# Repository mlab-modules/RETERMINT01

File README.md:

# RETERMINT01 – RETERMINAL DM Interface Board

<div align="center">

</div>

RETERMINT01 is an interface board for the [reTerminal DM](https://wiki.seeedstudio.com/reterminal-dm/) by Seeed Studio. It adds a galvanically isolated industrial interface — **3× RS-485** bus, **isolated 24 V power supply** and the ability to **remotely switch off the power** of a connected field device via GPIO. All communication on the bus side is fully galvanically isolated from the reTerminal DM logic.

The board connects directly to the 40-pin GPIO header of the reTerminal DM.

## Features

- **3× RS-485** – galvanically isolated half-duplex channels (ADM2483xRW), up to 500 kbps
- **Isolated 24 V DC/DC** – 30 W Traco Power THN 30-2423WI, software-controllable (default OFF)
- **Remote power switching** – PS1 output controlled via `PWR_OFF` GPIO signal (active LOW)
- **5 V power module** – TI TPSM33606S5, powers the isolated RS-485 bus side
- **u-blox NEO-M9N GPS** – with u.FL antenna connector, USB configuration port and 1 F supercapacitor backup
- **Shielded RJ45 with LEDs** – for RS-485 field bus connection
- **ESD & overvoltage protection** – SM712 TVS on every RS-485 channel, USBLC6-2SC6 on GPS USB
- **2× 1 A fuse** – on 24 V input paths

## Schematic

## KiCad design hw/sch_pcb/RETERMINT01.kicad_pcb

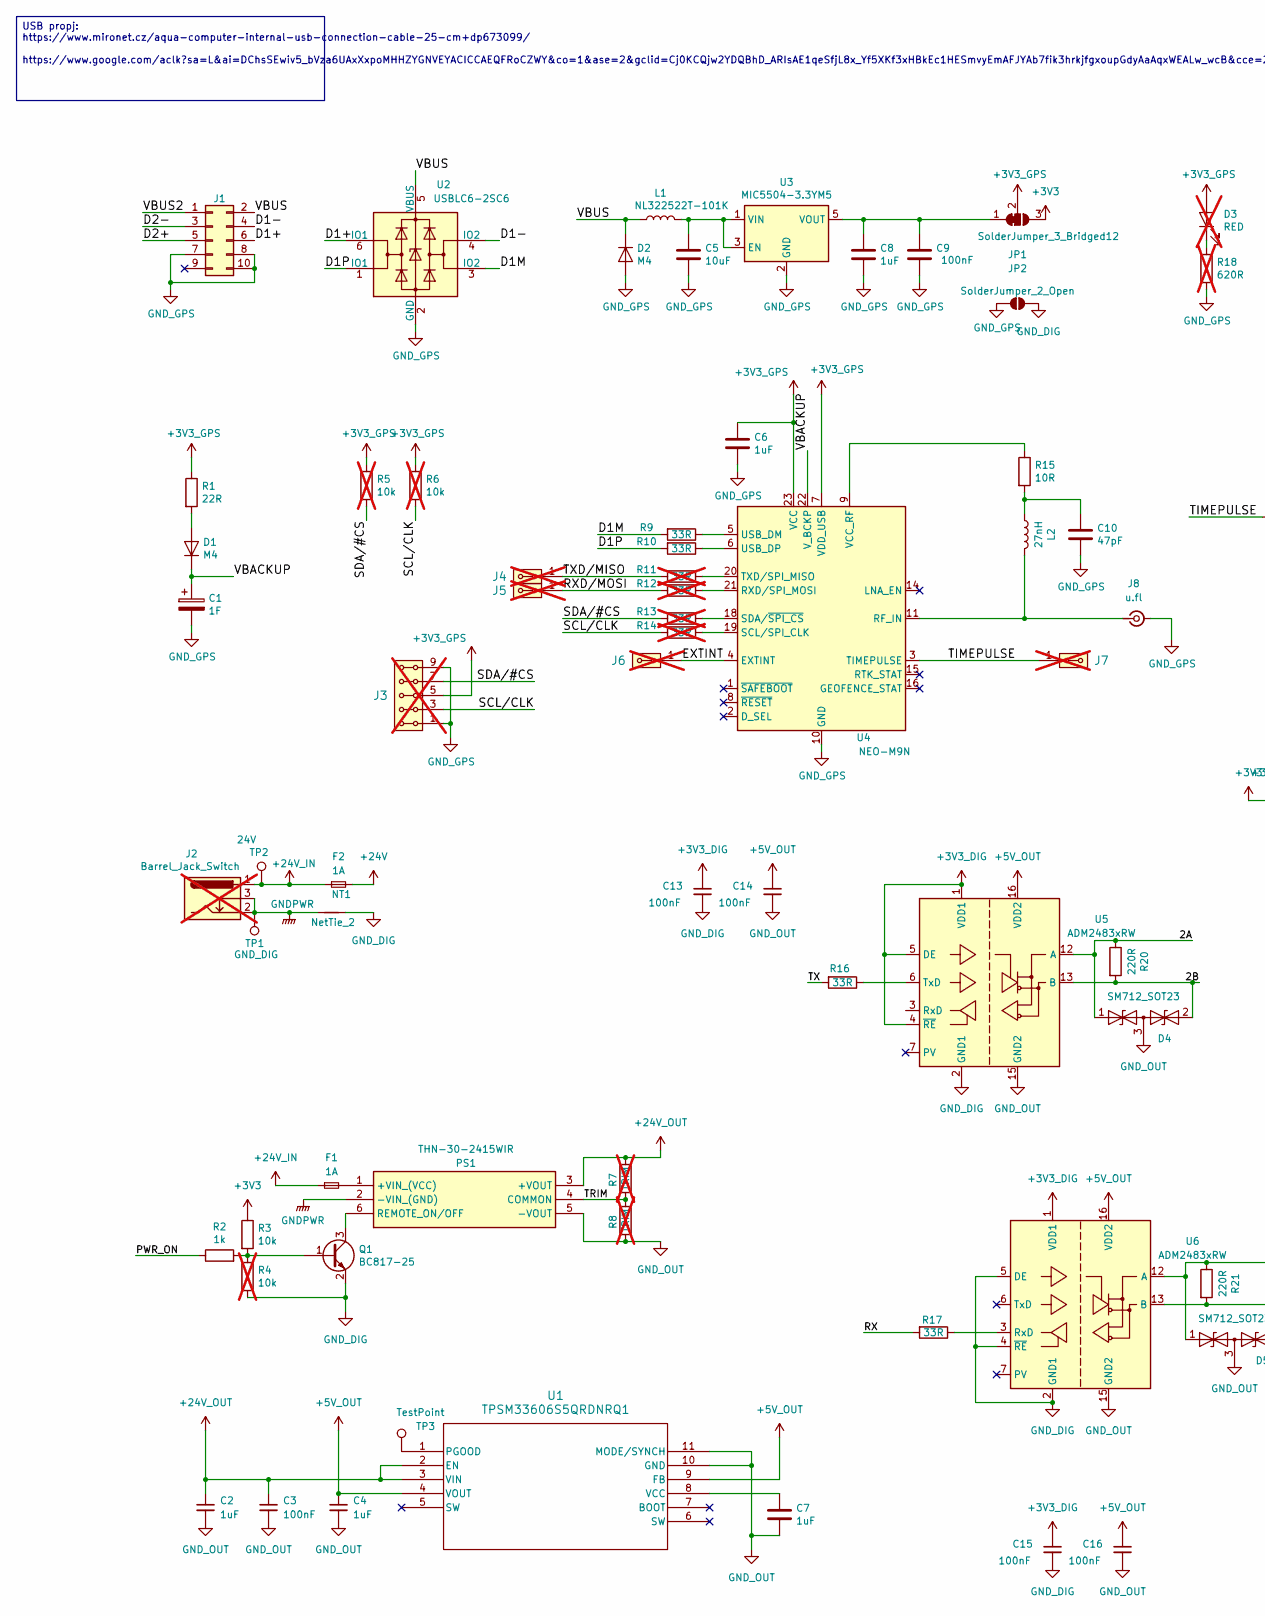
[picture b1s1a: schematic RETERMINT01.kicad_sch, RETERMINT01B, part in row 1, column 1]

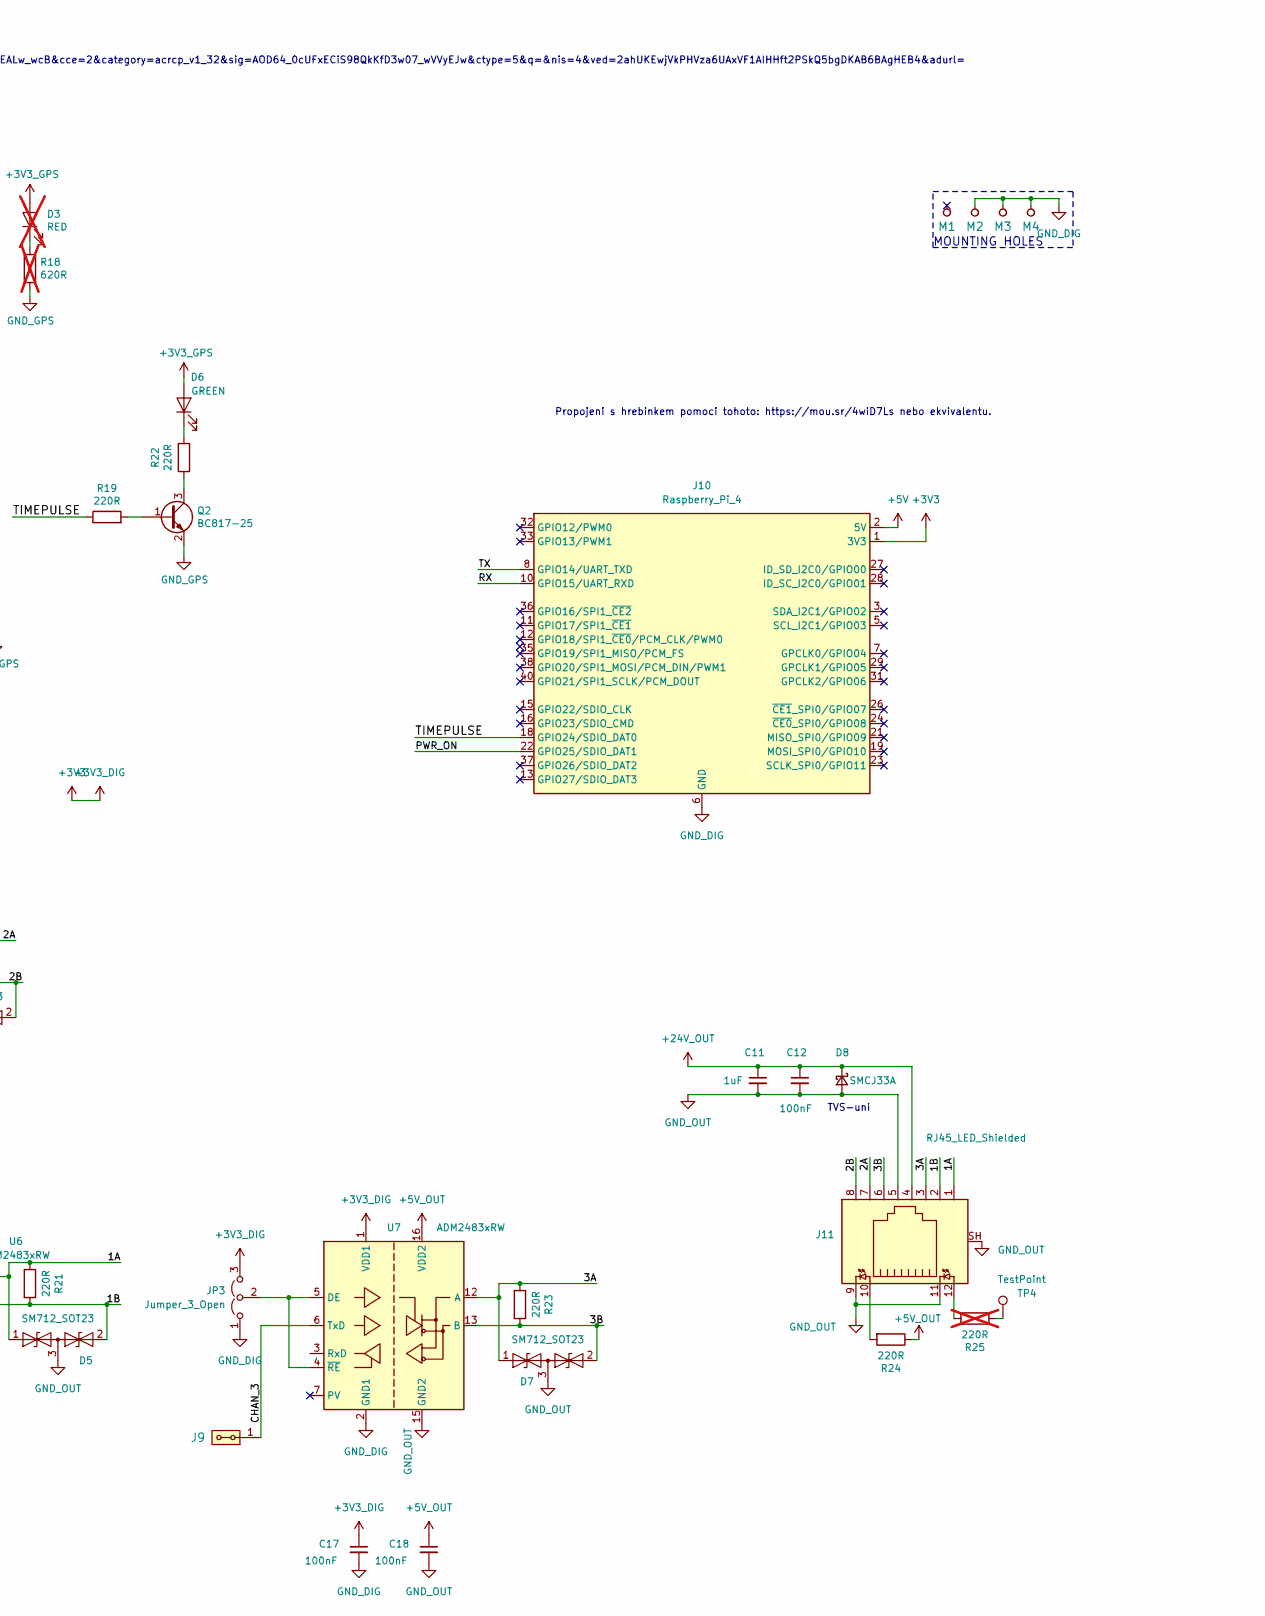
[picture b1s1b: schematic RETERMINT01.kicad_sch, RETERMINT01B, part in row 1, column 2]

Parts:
C1: 1F; CP_Radial_D8.0mm_P3.50mm
C2, C4, C6, C7, C8, C11: 1uF; C_0805_2012Metric
C3, C9, C12, C13, C14, C15, C16, C17, C18: 100nF; C_0805_2012Metric
C5: 10uF; C_0805_2012Metric
C10: 47pF; C_0805_2012Metric
D1, D2: M4; D_SMA
D3: RED; LED_1206_3216Metric; not fitted
D4, D5, D7: SM712_SOT23; SOT-23
D6: GREEN; LED_1206_3216Metric
D8: SMCJ33A; D_SMC
F1, F2: 1A; Fuse_0805_2012Metric
J1: Conn_02x05_Odd_Even; PinHeader_2x05_P2.54mm_Vertical
J2: Barrel_Jack_Switch; BarrelJack_Horizontal; not fitted
J3: HEADER_2x05_PARALLEL; Straight_2x05; not fitted
J4, J5, J6, J7: HEADER_2x01_PARALLEL; Straight_2x01; not fitted
J8: u.fl; U.FL_Molex_MCRF_73412-0110_Vertical
J9: HEADER_2x01_PARALLEL; Straight_2x01
J10: Raspberry_Pi_4; PinHeader_2x20_P2.54mm_Vertical
J11: RJ45_LED_Shielded; RJ45_Amphenol_RJHSE538X
JP1: SolderJumper_3_Bridged12; SolderJumper-3_P1.3mm_Bridged12_RoundedPad1.0x1.5mm
JP2: SolderJumper_2_Open; SolderJumper-2_P1.3mm_Open_RoundedPad1.0x1.5mm
JP3: Jumper_3_Open; PinHeader_1x03_P2.54mm_Vertical
L1: NL322522T-101K; L_1210_3225Metric
L2: 27nH; L_0402_1005Metric
M1, M2, M3, M4: HOLE; MountingHole_3mm
NT1: NetTie_2; NetTie-2_SMD_Pad0.5mm
PS1: THN-30-2415WIR; Converter_DCDC_TRACO_THN30-xxxx_THT; Mouser Part Number 495-THN30-2415WIR
Q1, Q2: BC817-25; SOT-23
R1: 22R; R_0805_2012Metric
R2: 1k; R_0805_2012Metric
R3: 10k; R_0805_2012Metric
R4, R5, R6: 10k; R_0805_2012Metric; not fitted
R7, R8: TRIM; R_0805_2012Metric; not fitted
R9, R10, R16, R17: 33R; R_0805_2012Metric
R11, R12, R13, R14: 33R; R_0805_2012Metric; not fitted
R15: 10R; R_0805_2012Metric
R18: 620R; R_0805_2012Metric; not fitted
R19, R20, R21, R22, R23, R24: 220R; R_0805_2012Metric
R25: 220R; R_0805_2012Metric; not fitted
TP1: GND_DIG; Pin_D1.4mm_L8.5mm_W2.8mm_FlatFork
TP2: 24V; Pin_D1.4mm_L8.5mm_W2.8mm_FlatFork
TP3, TP4: TestPoint; TestPoint_Pad_D1.5mm
U1: TPSM33606S5QRDNRQ1; RDN0011A_TEX
U2: USBLC6-2SC6; SOT-23-6
U3: MIC5504-3.3YM5; SOT-23-5
U4: NEO-M9N; ublox_NEO
U5, U6, U7: ADM2483xRW; SOIC-16W_7.5x10.3mm_P1.27mm

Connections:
+3V3: C13.1, C15.1, C17.1, J10.1 (3V3), J10.17 (3V3), JP1.3 (B), JP3.3 (B), R3.1, U5.1 (VDD1), U5.4 (~RE), U5.5 (DE), U6.1 (VDD1), U7.1 (VDD1)
+3V3_GPS: C6.1, D3.2 (A), D6.2 (A), J3.5, J3.6, JP1.2 (C), R1.1, R5.1, R6.1, U4.7 (VDD_USB), U4.23 (VCC)
+5V: J10.2 (5V), J10.4 (5V)
+5V_OUT: C4.1, C14.1, C16.1, C18.1, R24.1, U1.4 (VOUT), U1.9 (FB), U5.16 (VDD2), U6.16 (VDD2), U7.16 (VDD2)
+24V: F2.2
+24V_IN: F1.1, F2.1, J2.1, TP2.1 (1_1)
+24V_OUT: C2.1, C3.1, C11.1, C12.1, D8.1 (K), J11.4, PS1.3 (+VOUT), R7.1, U1.2 (EN), U1.3 (VIN)
/1A: D5.1 (A1), J11.1, R21.1, U6.12 (A)
/1B: D5.2 (A2), J11.2, R21.2, U6.13 (B)
/2A: D4.1 (A1), J11.7, R20.1, U5.12 (A)
/2B: D4.2 (A2), J11.8, R20.2, U5.13 (B)
/3A: D7.1 (A1), J11.3, R23.1, U7.12 (A)
/3B: D7.2 (A2), J11.6, R23.2, U7.13 (B)
/CHAN_3: J9.1, J9.2, U7.6 (TxD)
/D1+: J1.6, U2.6 (IO1)
/D1-: J1.4, U2.4 (IO2)
/D1M: R9.2, U2.3 (IO2)
/D1P: R10.2, U2.1 (IO1)
/D2+: J1.5
/D2-: J1.3
/EXTINT: J6.1, J6.2, U4.4 (EXTINT)
/PWR_ON: J10.22 (GPIO25/SDIO_DAT1), R2.1
/RX: J10.10 (GPIO15/UART_RXD), R17.2
/RXD/MOSI: J5.1, J5.2, R12.2
/SCL/CLK: J3.3, J3.4, R6.2, R14.2
/SDA/#CS: J3.7, J3.8, R5.2, R13.2
/TIMEPULSE: J7.1, J7.2, J10.18 (GPIO24/SDIO_DAT0), R19.1, U4.3 (TIMEPULSE)
/TRIM: PS1.4 (COMMON), R7.2, R8.1
/TX: J10.8 (GPIO14/UART_TXD), R16.2
/TXD/MISO: J4.1, J4.2, R11.2
/VBACKUP: C1.1, D1.1 (K), U4.22 (V_BCKP)
/VBUS: D2.1 (K), J1.2, L1.1, U2.5 (VBUS)
/VBUS2: J1.1
GNDPWR: J2.2, J2.3, NT1.1, PS1.2 (-VIN_(GND)), TP1.1 (1_1)
GND_DIG: C13.2, C15.2, C17.2, J10.6 (GND), J10.9 (GND), J10.14 (GND), J10.20 (GND), J10.25 (GND), J10.30 (GND), J10.34 (GND), J10.39 (GND), JP2.2 (B), JP3.1 (A), M2.1, M3.1, M4.1, NT1.2, Q1.2 (E), R4.2, U5.2 (GND1), U5.8 (GND1), U6.2 (GND1), U6.4 (~RE), U6.5 (DE), U6.8 (GND1), U7.2 (GND1), U7.8 (GND1)
GND_GPS: C1.2, C5.2, C6.2, C8.2, C9.2, C10.2, D2.2 (A), J1.7, J1.8, J1.10, J3.1, J3.2, J3.9, J3.10, J8.2 (Ext), JP2.1 (A), Q2.2 (E), R18.2, U2.2 (GND), U3.2 (GND), U4.10 (GND), U4.12 (GND), U4.13 (GND), U4.24 (GND)
GND_OUT: C2.2, C3.2, C4.2, C7.2, C11.2, C12.2, C14.2, C16.2, C18.2, D4.3 (common), D5.3 (common), D7.3 (common), D8.2 (A), J11.5, J11.9, J11.11, J11.SH, PS1.5 (-VOUT), R8.2, U1.10 (GND), U1.11 (MODE/SYNCH), U5.9 (GND2), U5.15 (GND2), U6.9 (GND2), U6.15 (GND2), U7.9 (GND2), U7.15 (GND2)
unnamed: C10.1, L2.1, R15.2
unnamed: D1.2 (A), R1.2
unnamed: D3.1 (K), R18.1
unnamed: D6.1 (K), R22.2
unnamed: J8.1 (In), L2.2, U4.11 (RF_IN)
unnamed: J11.10, R24.2
unnamed: J11.12, R25.2
unnamed: C8.1, C9.1, JP1.1 (A), U3.5 (VOUT)
unnamed: JP3.2 (C), U7.4 (~RE), U7.5 (DE)
unnamed: F1.2, PS1.1 (+VIN_(VCC))
unnamed: PS1.6 (REMOTE_ON/OFF), Q1.3 (C)
unnamed: Q1.1 (B), R2.2, R3.2, R4.1
unnamed: Q2.1 (B), R19.2
unnamed: Q2.3 (C), R22.1
unnamed: R25.1, TP4.1 (1_1)
unnamed: TP3.1 (1_1), U1.1 (PGOOD)
unnamed: C7.1, U1.8 (VCC)
unnamed: C5.1, L1.2, U3.1 (VIN), U3.3 (EN)
unnamed: R12.1, U4.21 (RXD/SPI_MOSI)
unnamed: R14.1, U4.19 (SCL/SPI_CLK)
unnamed: R13.1, U4.18 (SDA/~SPI_CS)
unnamed: R11.1, U4.20 (TXD/SPI_MISO)
unnamed: R9.1, U4.5 (USB_DM)
unnamed: R10.1, U4.6 (USB_DP)
unnamed: R15.1, U4.9 (VCC_RF)
unnamed: R16.1, U5.6 (TxD)
unnamed: R17.1, U6.3 (RxD)

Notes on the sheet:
Propojeni s hrebinkem pomoci tohoto: https://mou.sr/4wiD7Ls nebo ekvivalentu.
TVS-uni
MOUNTING HOLES
USB propj: https://www.mironet.cz/aqua-computer-internal-usb-connection-cable-25-cm+dp673099/ https://www.google.com/aclk?sa=L&ai=DChsSEwiv5_bVza6UAxXxpoMHHZYGNVEYACICCAEQFRoCZWY&co=1&ase=2&gclid=Cj0KCQjw2YDQBhD_ARIsAE1qeSfjL8x_Yf5XKf3xHBkEc1HESmvyEmAFJYAb7fik3hrkjfgxoupGdyAaAqxWEALw_wcB&cce=2&cate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

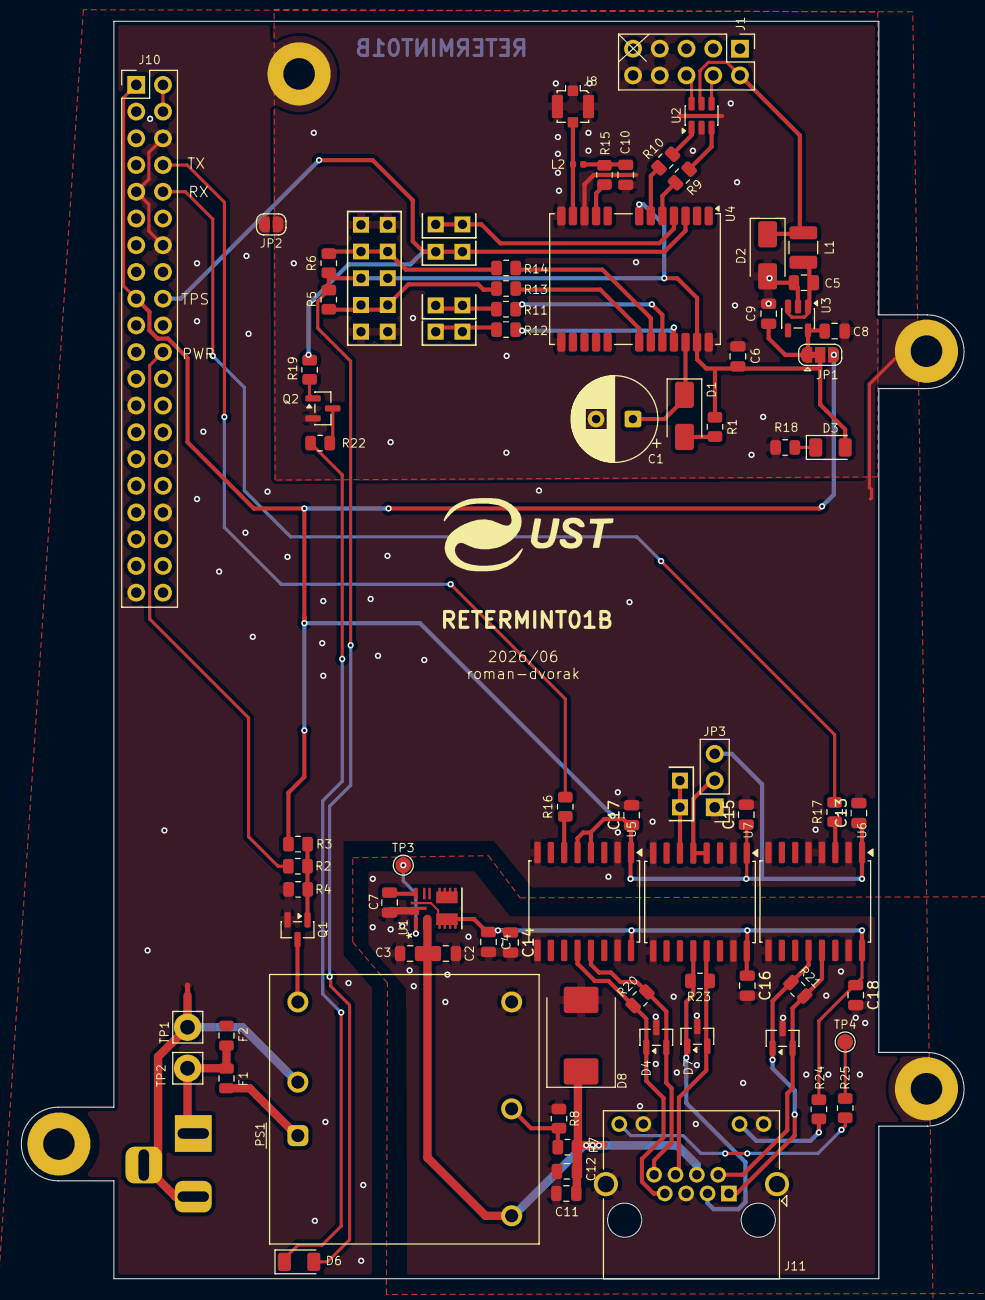
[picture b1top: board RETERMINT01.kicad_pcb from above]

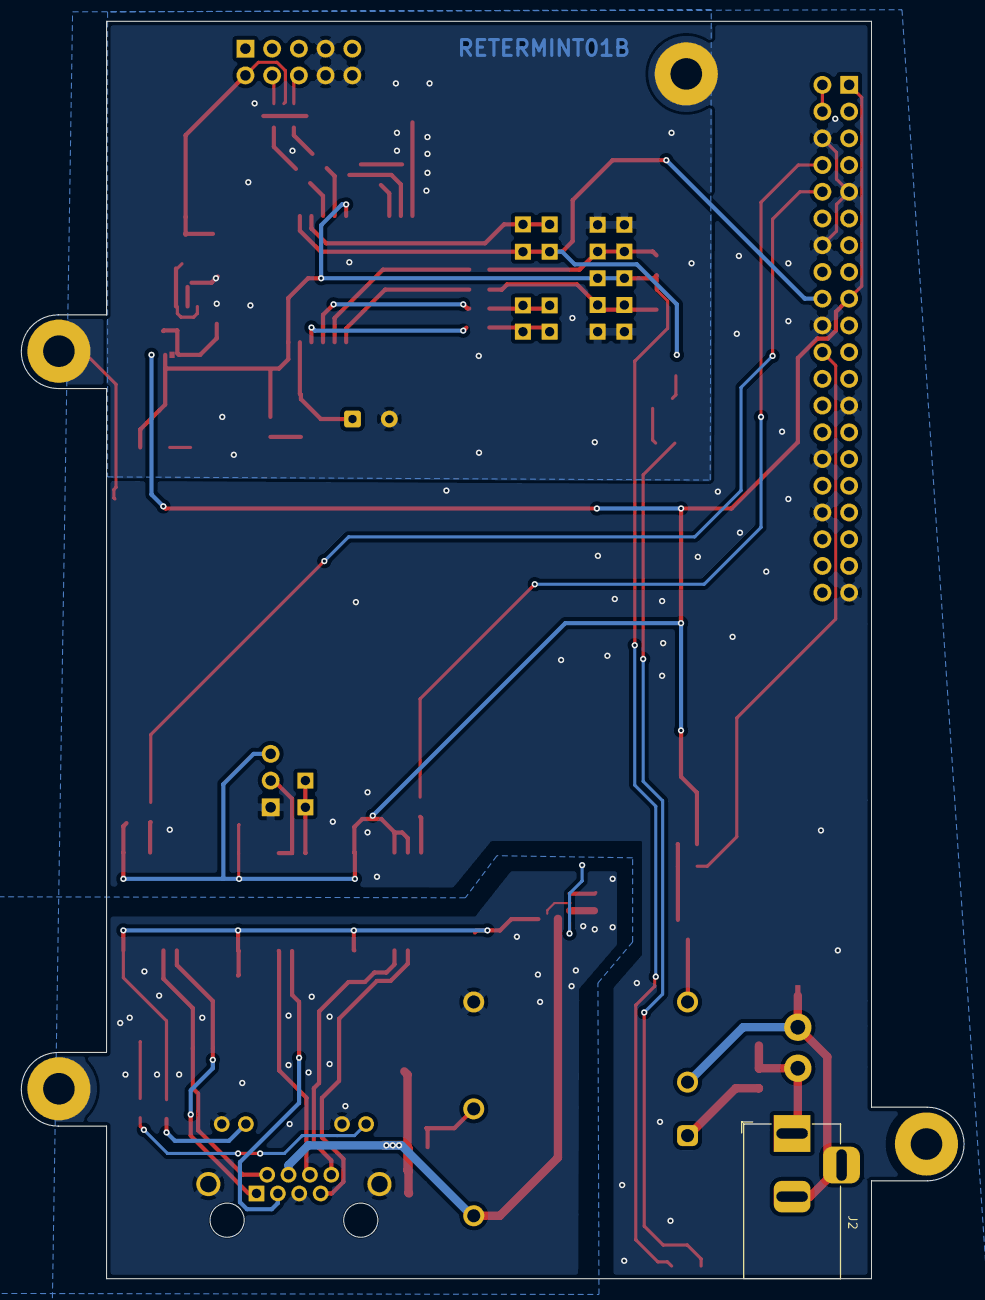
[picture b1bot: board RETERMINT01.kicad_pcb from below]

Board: 2 copper layers, 89.6 x 119.5 mm, 88 parts (2 on the bottom side), 60 nets.

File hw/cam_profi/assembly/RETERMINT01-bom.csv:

Component,Description,Part,References,Value,Footprint,Quantity Per PCB,Datasheet,ust_id,height,mouser part number,mouser price/stock,manufacturer_name,manufacturer_part_number
1,,C-Device,C10,47pF,C_0805_2012Metric,1,,5c70984712875079b91f8b38,,,,,
2,"Unpolarized capacitor, small symbol",C_Small,C3C12,100nF,C_0805_2012Metric,2,,5c70984712875079b91f8b4c,,,,,
3,,C-Device,C9,100nF,C_0805_2012Metric,1,,5c70984712875079b91f8b4c,,,,,
4,"Unpolarized capacitor, small symbol",C_Small,C2C4C11,1uF,C_0805_2012Metric,3,,5c70984712875079b91f8b50,,,,,
5,,C-Device,C6C7C8,1uF,C_0805_2012Metric,3,,5c70984712875079b91f8b50,,,,,
6,,C-Device,C5,10uF,C_0805_2012Metric,1,,5c70984812875079b91f8bbe,,,,,
7,,CP-Device,C1,1F,CP_Radial_D8.0mm_P3.50mm,1,,5c70984412875079b91f8873,,,,,
8,,LED-Device,D6,GREEN,LED_1206_3216Metric,1,,5c70984412875079b91f8895,,,,,
9,,D-Device,D1D2,M4,D_SMA,2,,5c70984512875079b91f88ac,,,,,
10,"7V/12V, 600W Asymmetrical TVS Diode Array, SOT-23",SM712_SOT23,D4D5D7,SM712_SOT23,SOT-23,3,https://www.littelfuse.com/~/media/electronics/datasheets/tv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,?,,,,,
11,"Schottky diode, small symbol",D_Schottky_Small,D8,SMCJ33A,D_SMC,1,,,,,,,
12,"Fuse, small symbol",Fuse_Small,F1F2,1A,Fuse_0805_2012Metric,2,,,,,,,
13,"Generic connector, double row, 02x05, odd/even pin numbering scheme (row 1 odd numbers, row 2 even numbers), script generated (kicad-library-utils/schlib/autogen/connector/)",Conn_02x05_Odd_Even,J1,Conn_02x05_Odd_Even,PinHeader_2x05_P2.54mm_Vertical,1,,,,,,,
14,"2x01 2.54 mm pitch header, 2 pins next to each other are connected",HEADER_2x01_PARALLEL,J9,HEADER_2x01_PARALLEL,Straight_2x01,1,,,,,,,
15,"RJ connector, 8P8C (8 positions 8 connected), two LEDs, Shielded",RJ45_LED_Shielded,J11,RJ45_LED_Shielded,RJ45_Amphenol_RJHSE538X,1,,,,,,,
16,Raspberry Pi 4 Model B,Raspberry_Pi_4,J10,Raspberry_Pi_4,PinHeader_2x20_P2.54mm_Vertical,1,https://datasheets.raspberrypi.com/rpi4/raspberry-pi-4-datas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,,,,,,
17,"small coaxial connector (BNC, SMA, SMB, SMC, Cinch/RCA, LEMO, ...)",Conn_Coaxial_Small,J8,u.fl,U.FL_Molex_MCRF_73412-0110_Vertical,1,,5ed7ac8e12875004e15a62c8,,,,,
18,,L-Device,L2,27nH,L_0402_1005Metric,1,LQG15HS27NJ02D,618cbf071287506e2801ed7e,,,,,
19,,L-Device,L1,NL322522T-101K,L_1210_3225Metric,1,,5c70984412875079b91f87fb,,,,,
20,"30 Watt DC/DC converter, industrial, 4:1 input, encpasulated, 1.0"" x 1.0"" metal package",THN_30-2423WI,PS1,THN-30-2415WIR,Converter_DCDC_TRACO_THN30-xxxx_THT,1,https://tracopower.com/thn30wi-datasheet/,,10.4,495-THN30-2415WIR,https://www.mouser.co.uk/ProductDetail/TRACO-Power/THN-30-24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,Traco Power,THN-30-2415WIR
21,"NPN transistor, base/emitter/collector",Q_NPN_BEC,Q1Q2,BC817-25,SOT-23,2,,5c70984712875079b91f8aea,,,,,
22,,R-Device,R15,10R,R_0805_2012Metric,1,,5c70984512875079b91f896d,,,,,
23,,R-Device,R1,22R,R_0805_2012Metric,1,,5c70984512875079b91f896f,,,,,
24,,R-Device,R9R10R16R17,33R,R_0805_2012Metric,4,,5c70984512875079b91f8970,,,,,
25,Resistor,R,R19R20R21R22R23R24,220R,R_0805_2012Metric,6,,5c70984512875079b91f897f,,,,,
26,Resistor,R,R2,1k,R_0805_2012Metric,1,,5c70984512875079b91f898c,,,,,
27,,R-Device,R3,10k,R_0805_2012Metric,1,,5c70984612875079b91f899f,,,,,
28,"Isolated RS485/RS422 Transceiver, Half-Duplex, 500kbps, SOIC-16W",ADM2483xRW,U5U6U7,ADM2483xRW,SOIC-16W_7.5x10.3mm_P1.27mm,3,https://www.analog.com/media/en/technical-documentation/data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,,,,,,
29,,MIC5504-3.3YM5-Regulator_Linear,U3,MIC5504-3.3YM5,SOT-23-5,1,http://ww1.microchip.com/downloads/en/DeviceDoc/MIC550X.pdf,5c7255e81287500b4e112ea2,,,,,
30,,NEO-M8P-RF_GPS,U4,NEO-M9N,ublox_NEO,1,https://www.u-blox.com/sites/default/files/NEO-M8P_DataSheet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,5fa0faaf12875025b3977985,,,,,
31,,TPSM33606S5QRDNRQ1,U1,TPSM33606S5QRDNRQ1,RDN0011A_TEX,1,https://www.ti.com/lit/gpn/tpsm33606-q1,,,,,,
32,,USBLC6-2SC6-Power_Protection,U2,USBLC6-2SC6,SOT-23-6,1,http://www2.st.com/resource/en/datasheet/CD00050750.pdf,5e82e0691287502a334a778c,,,,,

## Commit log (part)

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2026-05-10 initial version of RETERMINAL DM interface module
2026-05-10 Update metadata files
2026-05-11 Update workflow files
2026-05-11 Automatic update of KiCAD outputs
2026-05-18 wip, layout
2026-05-18 Fix D1 symbol type, fill title block
2026-05-18 PS1 default-off: add pull-up on Q1 base, rework R2/R3
2026-05-18 Add comprehensive README
2026-05-18 Rework README: update intro, SVG schematic, remove block diagram and license
2026-05-18 Use div for PCB images instead of table
2026-05-18 Translate README intro and features to English
2026-05-18 update actions
2026-05-18 update layout
2026-05-18 ci: pin doc/assets to KiCADv9 branch + bump to current HEAD
    - .gitmodules: track KiCADv9 (matches the KiCad version actually
    used). Without this, `git submodule update --remote` in
    update_actions.yml would pull KiCADv10 (submodule default branch)
    and silently swap kibot/workflow files.
    - doc/assets: bump f49c1a5 -> 3c591db (latest KiCADv9, includes
    the v2_dk9 workflow template).
2026-05-18 update hader position
2026-05-26 Update DC/DC label
2026-05-27 Update submodule to UST assets.
2026-05-27 Fix #2 Fix DRC errors. Improve layout.
2026-05-27 Update actions products
2026-05-31 Update component values.
2026-06-25 fix issues
2026-06-25 update assets
